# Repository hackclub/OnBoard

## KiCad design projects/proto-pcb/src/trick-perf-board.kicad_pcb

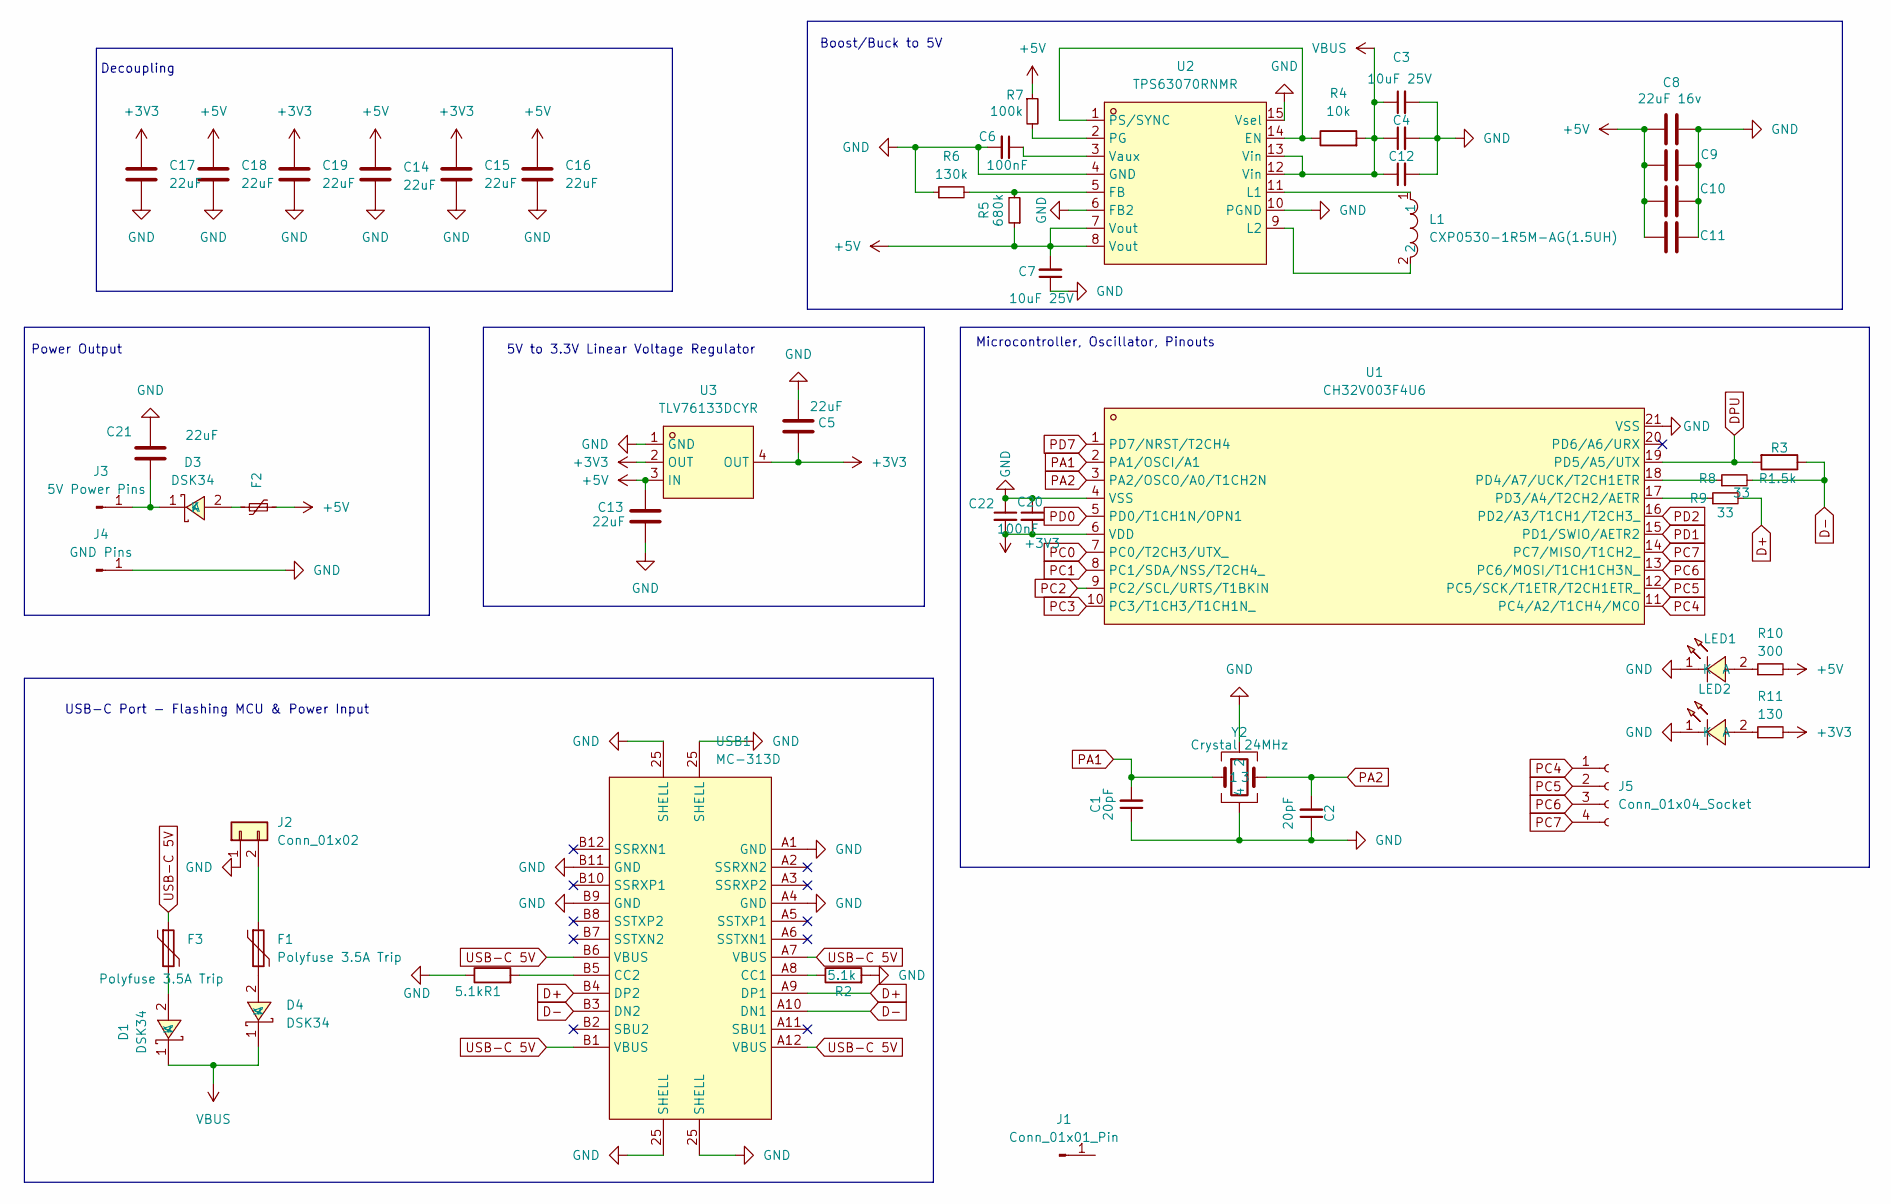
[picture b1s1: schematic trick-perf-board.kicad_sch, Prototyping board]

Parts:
C1, C2: 20pF; C_0402_1005Metric; LCSC C880615
C3, C4, C7, C12: 10uF 25V; C_0603_1608Metric; LCSC Part C7393892
C5, C13, C21: 22uF; C_0603_1608Metric; LCSC Part C6119880
C6, C20, C22: 100nF; C_0402_1005Metric; LCSC Part C392963
C8, C9, C10, C11: 22uF 16v; C_0603_1608Metric; LCSC Part C6119868
C14, C15, C16, C17, C18, C19: 22uF; C_0805_2012Metric; LCSC Part C6119899
D1, D3, D4: DSK34; SOD-123_L2.8-W1.8-LS3.7-RD; LCSC Part C41029
F1, F3: Polyfuse 3.5A Trip; Fuse_1206_3216Metric; LCSC Part C2982271
F2: Polyfuse_Small; Fuse_0603_1608Metric; LCSC Part C2830225
J1: Conn_01x01_Pin; LargePerfBoard
J2: Conn_01x02; PinSocket_1x02_P2.54mm_Horizontal
J3: 5V Power Pins; customPerfBoardpins
J4: GND Pins; customPerfBoardpins
J5: Conn_01x04_Socket; PinHeader_1x04_P2.54mm_Vertical
L1: CXP0530-1R5M-AG(1.5UH); L_0603_1608Metric; LCSC Part C7461358
LED1, LED2: TZ-P2-0402RTIA1-0.45T; LED0402-RD_RED; LCSC Part C779449
R1, R2: 5.1k; R_0402_1005Metric; LCSC Part C103086
R3: R1.5k; R_0402_1005Metric; LCSC Part C2929900
R4: 10k; R_0402_1005Metric; LCSC Part C2906885
R5: 680k; R_0402_1005Metric; LCSC Part C3017522
R6: 130k; R_0402_1005Metric; LCSC Part C2909318
R7: 100k; R_0402_1005Metric; LCSC Part C2759534
R8, R9: 33; R_0402_1005Metric; LCSC Part C2906931
R10: 300; R_0402_1005Metric; LCSC Part C352438
R11: 130; R_0402_1005Metric; LCSC Part C352478
U1: CH32V003F4U6; QFN-20-1EP_3x3mm_P0.4mm_EP1.65x1.65mm; LCSC Part C5299908
U2: TPS63070RNMR; VQFN-HR-15_L3.0-W2.5-P0.50-BL_TPS63070RNMR; LCSC Part C109322
U3: TLV76133DCYR; SOT-223-4_L6.5-W3.5-P2.30-LS7.0-TR; LCSC Part C7527500
USB1: MC-313D; TYPE-C-TH_MC-313D; LCSC Part C428461
Y2: Crystal 24MHz; Crystal_SMD_2016-4Pin_2.0x1.6mm; LCSC Part C2875241

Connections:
+3V3: C5.1, C15.1, C17.1, C19.1, C20.2, C22.2, R11.2, U1.6 (VDD), U3.2 (OUT), U3.4 (OUT)
+5V: C7.2, C8.1, C9.1, C10.1, C11.1, C13.1, C14.1, C16.1, C18.1, F2.2, R5.1, R7.1, R10.2, U2.7 (Vout), U2.8 (Vout), U3.3 (IN)
D+: R9.2, USB1.A9 (DP1), USB1.B4 (DP2)
D-: R3.1, R8.2, USB1.A10 (DN1), USB1.B3 (DN2)
DPU: R3.2, U1.19 (PD5/A5/UTX)
GND: C1.1, C2.1, C3.2, C4.2, C5.2, C6.2, C7.1, C8.2, C9.2, C10.2, C11.2, C12.2, C13.2, C14.2, C15.2, C16.2, C17.2, C18.2, C19.2, C20.1, C21.1, C22.1, J2.1, J4.1, LED1.1 (K), LED2.1 (K), R1.1, R2.2, R6.1, U1.4 (VSS), U1.21 (VSS), U2.4 (GND), U2.6 (FB2), U2.10 (PGND), U2.15 (Vsel), U3.1 (GND), USB1.25 (SHELL), USB1.A1 (GND), USB1.A4 (GND), USB1.B9 (GND), USB1.B11 (GND), Y2.2, Y2.4
unnamed: D1.2 (A), F3.2
unnamed: D3.2 (A), F2.1
unnamed: C21.2, D3.1 (K), J3.1
unnamed: D4.2 (A), F1.2
unnamed: F1.1, J2.2
unnamed: LED1.2 (A), R10.1
unnamed: LED2.2 (A), R11.1
unnamed: R9.1, U1.17 (PD3/A4/T2CH2/AETR)
unnamed: R8.1, U1.18 (PD4/A7/UCK/T2CH1ETR)
unnamed: R4.1, U2.1 (PS/SYNC), U2.14 (EN)
unnamed: R5.2, R6.2, U2.5 (FB)
unnamed: L1.1, U2.11 (L1)
unnamed: L1.2, U2.9 (L2)
unnamed: R7.2, U2.2 (PG)
unnamed: C6.1, U2.3 (Vaux)
unnamed: R2.1, USB1.A8 (CC1)
unnamed: R1.2, USB1.B5 (CC2)
PA1: C1.2, U1.2 (PA1/OSCI/A1), Y2.1
PA2: C2.2, U1.3 (PA2/OSCO/A0/T1CH2N), Y2.3
PC0: U1.7 (PC0/T2CH3/UTX_)
PC1: U1.8 (PC1/SDA/NSS/T2CH4_)
PC2: U1.9 (PC2/SCL/URTS/T1BKIN)
PC3: U1.10 (PC3/T1CH3/T1CH1N_)
PC4: J5.1, U1.11 (PC4/A2/T1CH4/MCO)
PC5: J5.2, U1.12 (PC5/SCK/T1ETR/T2CH1ETR_)
PC6: J5.3, U1.13 (PC6/MOSI/T1CH1CH3N_)
PC7: J5.4, U1.14 (PC7/MISO/T1CH2_)
PD0: U1.5 (PD0/T1CH1N/OPN1)
PD1: U1.15 (PD1/SWIO/AETR2)
PD2: U1.16 (PD2/A3/T1CH1/T2CH3_)
PD7: U1.1 (PD7/NRST/T2CH4)
USB-C 5V: F3.1, USB1.A7 (VBUS), USB1.A12 (VBUS), USB1.B1 (VBUS), USB1.B6 (VBUS)
VBUS: C3.1, C4.1, C12.1, D1.1 (K), D4.1 (K), R4.2, U2.12 (Vin), U2.13 (Vin)

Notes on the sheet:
Microcontroller, Oscillator, Pinouts
5V to 3.3V Linear Voltage Regulator
Decoupling
USB-C Port - Flashing MCU & Power Input
Boost/Buck to 5V
Power Output

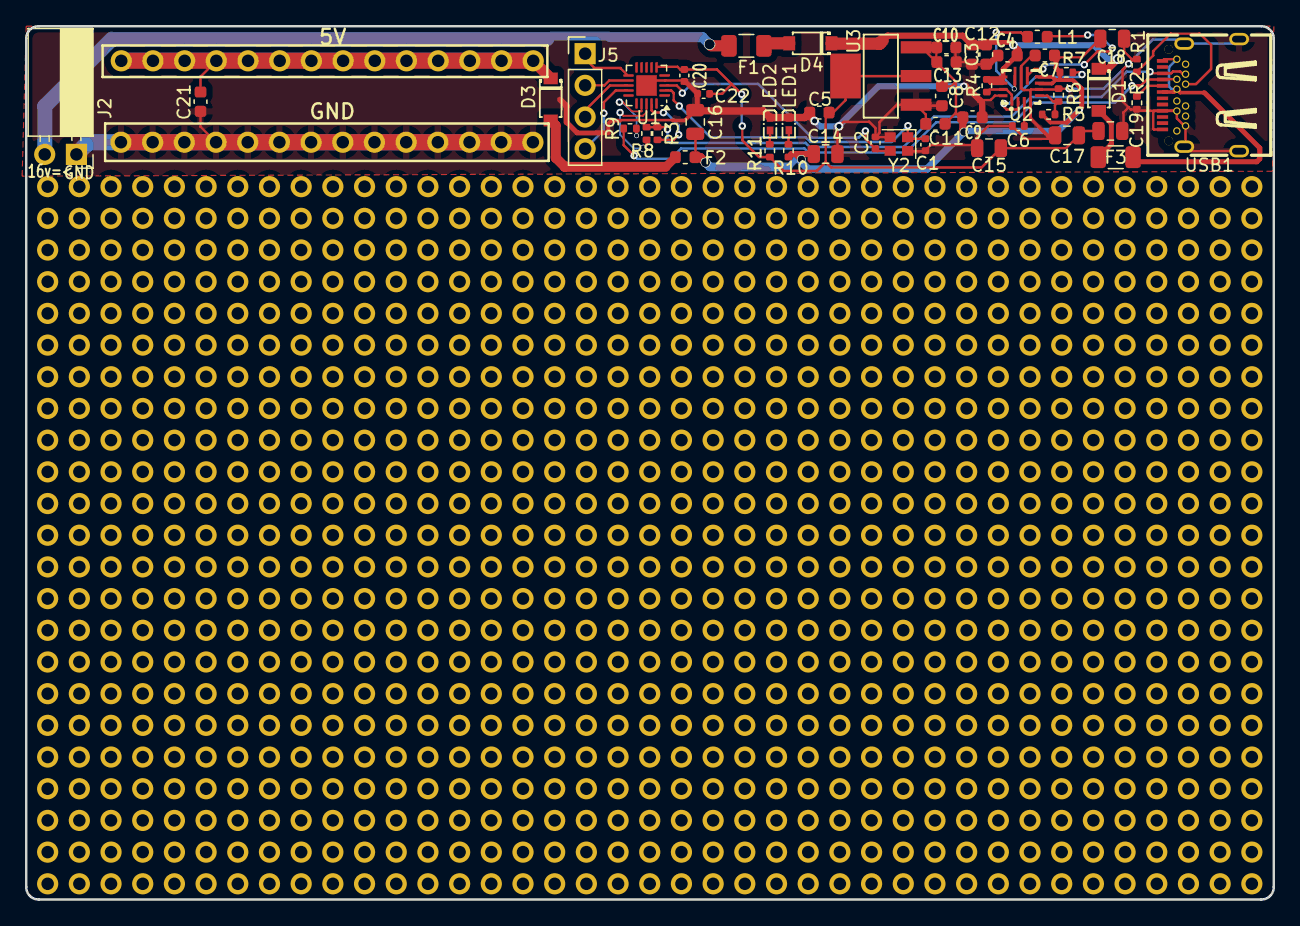
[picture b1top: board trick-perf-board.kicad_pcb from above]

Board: 2 copper layers, 100.0 x 70.0 mm, 52 parts (0 on the bottom side), 31 nets.

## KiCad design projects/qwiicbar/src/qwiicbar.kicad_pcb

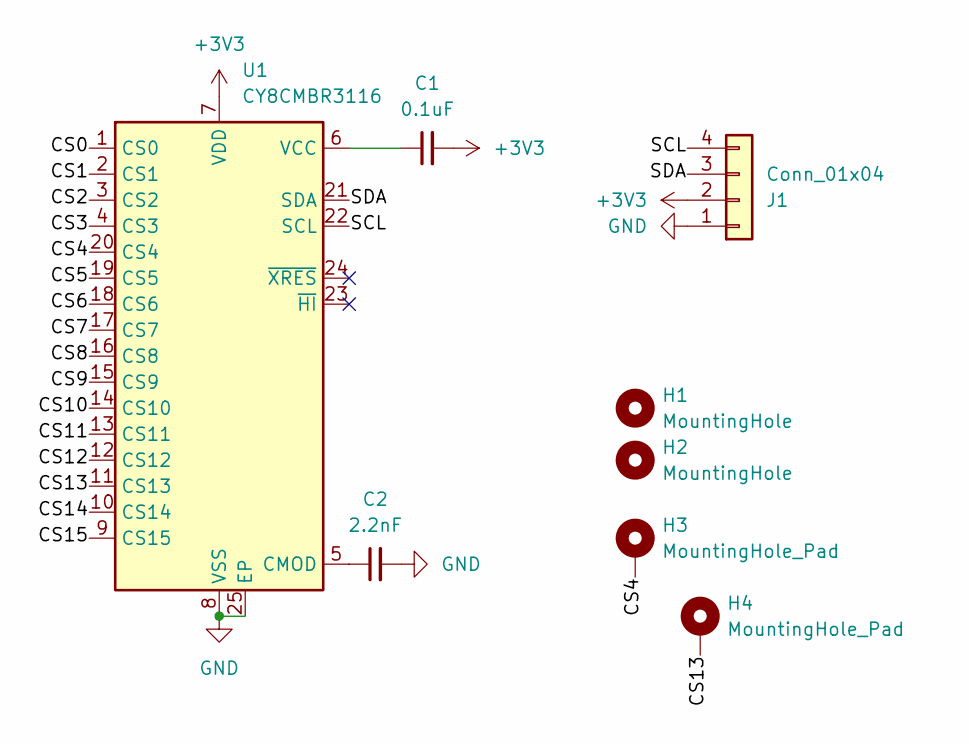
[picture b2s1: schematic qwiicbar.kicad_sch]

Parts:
C1: 0.1uF; C_0603_1608Metric
C2: 2.2nF; C_0805_2012Metric
H1, H2: MountingHole; JLCPCB_PCBA_ToolingHole
H3, H4: MountingHole_Pad; MountingHole_2.2mm_M2_ISO7380_Pad
J1: Conn_01x04; JST_SH_SM04B-SRSS-TB_1x04-1MP_P1.00mm_Horizontal
U1: CY8CMBR3116; QFN-24-1EP_4x4mm_P0.5mm_EP2.6x2.6mm

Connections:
+3V3: C1.2, J1.2, U1.7 (VDD)
/CS0: U1.1 (CS0)
/CS1: U1.2 (CS1)
/CS2: U1.3 (CS2)
/CS3: U1.4 (CS3)
/CS4: H3.1, U1.20 (CS4)
/CS5: U1.19 (CS5)
/CS6: U1.18 (CS6)
/CS7: U1.17 (CS7)
/CS8: U1.16 (CS8)
/CS9: U1.15 (CS9)
/CS10: U1.14 (CS10)
/CS11: U1.13 (CS11)
/CS12: U1.12 (CS12)
/CS13: H4.1, U1.11 (CS13)
/CS14: U1.10 (CS14)
/CS15: U1.9 (CS15)
/SCL: J1.4, U1.22 (SCL)
/SDA: J1.3, U1.21 (SDA)
GND: C2.2, J1.1, U1.8 (VSS), U1.25 (EP)
unnamed: C2.1, U1.5 (CMOD)
unnamed: C1.1, U1.6 (VCC)

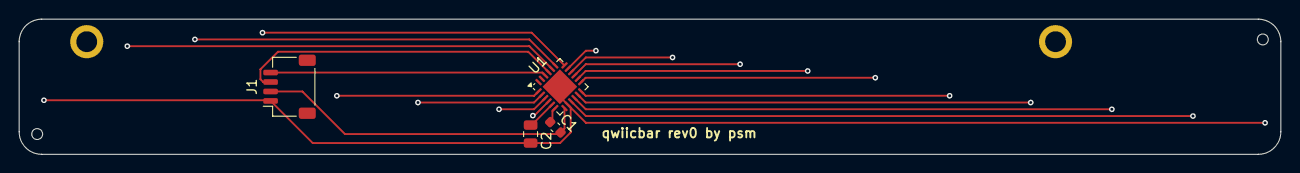
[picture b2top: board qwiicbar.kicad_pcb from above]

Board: 2 copper layers, 133.3 x 14.3 mm, 8 parts (0 on the bottom side), 8 nets.

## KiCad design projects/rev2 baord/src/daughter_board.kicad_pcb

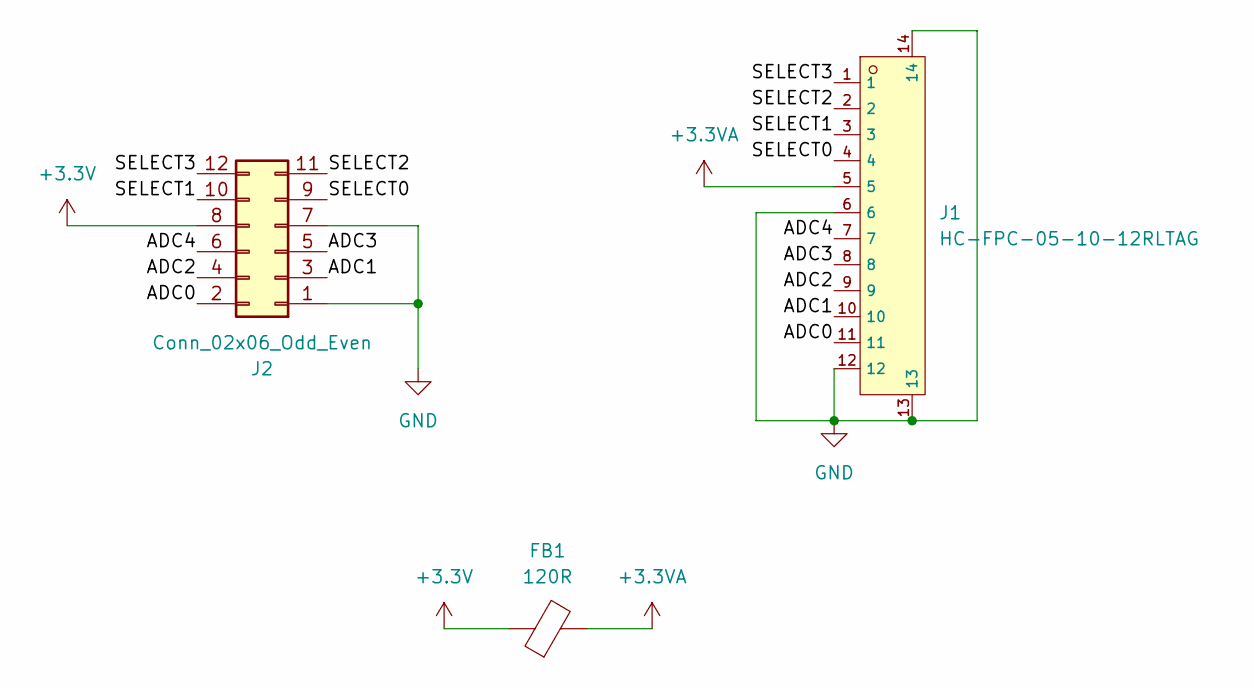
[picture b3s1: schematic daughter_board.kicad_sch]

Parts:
FB1: 120R; L_0603_1608Metric_Pad1.05x0.95mm_HandSolder; LCSC C76892
J1: HC-FPC-05-10-12RLTAG; FPC-SMD_12P-P0.50_HCTL_HC-FPC-05-10-12RLTAG; LCSC C5213732
J2: Conn_02x06_Odd_Even; PinHeader_2x06_P2.54mm_Horizontal

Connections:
+3.3V: FB1.1, J2.8
+3.3VA: FB1.2, J1.5
/ADC0: J1.11, J2.2
/ADC1: J1.10, J2.3
/ADC2: J1.9, J2.4
/ADC3: J1.8, J2.5
/ADC4: J1.7, J2.6
/SELECT0: J1.4, J2.9
/SELECT1: J1.3, J2.10
/SELECT2: J1.2, J2.11
/SELECT3: J1.1, J2.12
GND: J1.6, J1.12, J1.13, J1.14, J2.1, J2.7

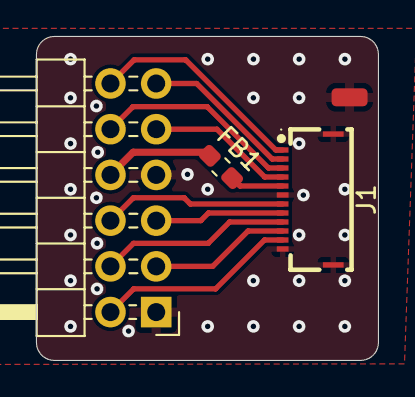
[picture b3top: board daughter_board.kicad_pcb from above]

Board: 2 copper layers, 19.0 x 18.0 mm, 3 parts (0 on the bottom side), 12 nets.

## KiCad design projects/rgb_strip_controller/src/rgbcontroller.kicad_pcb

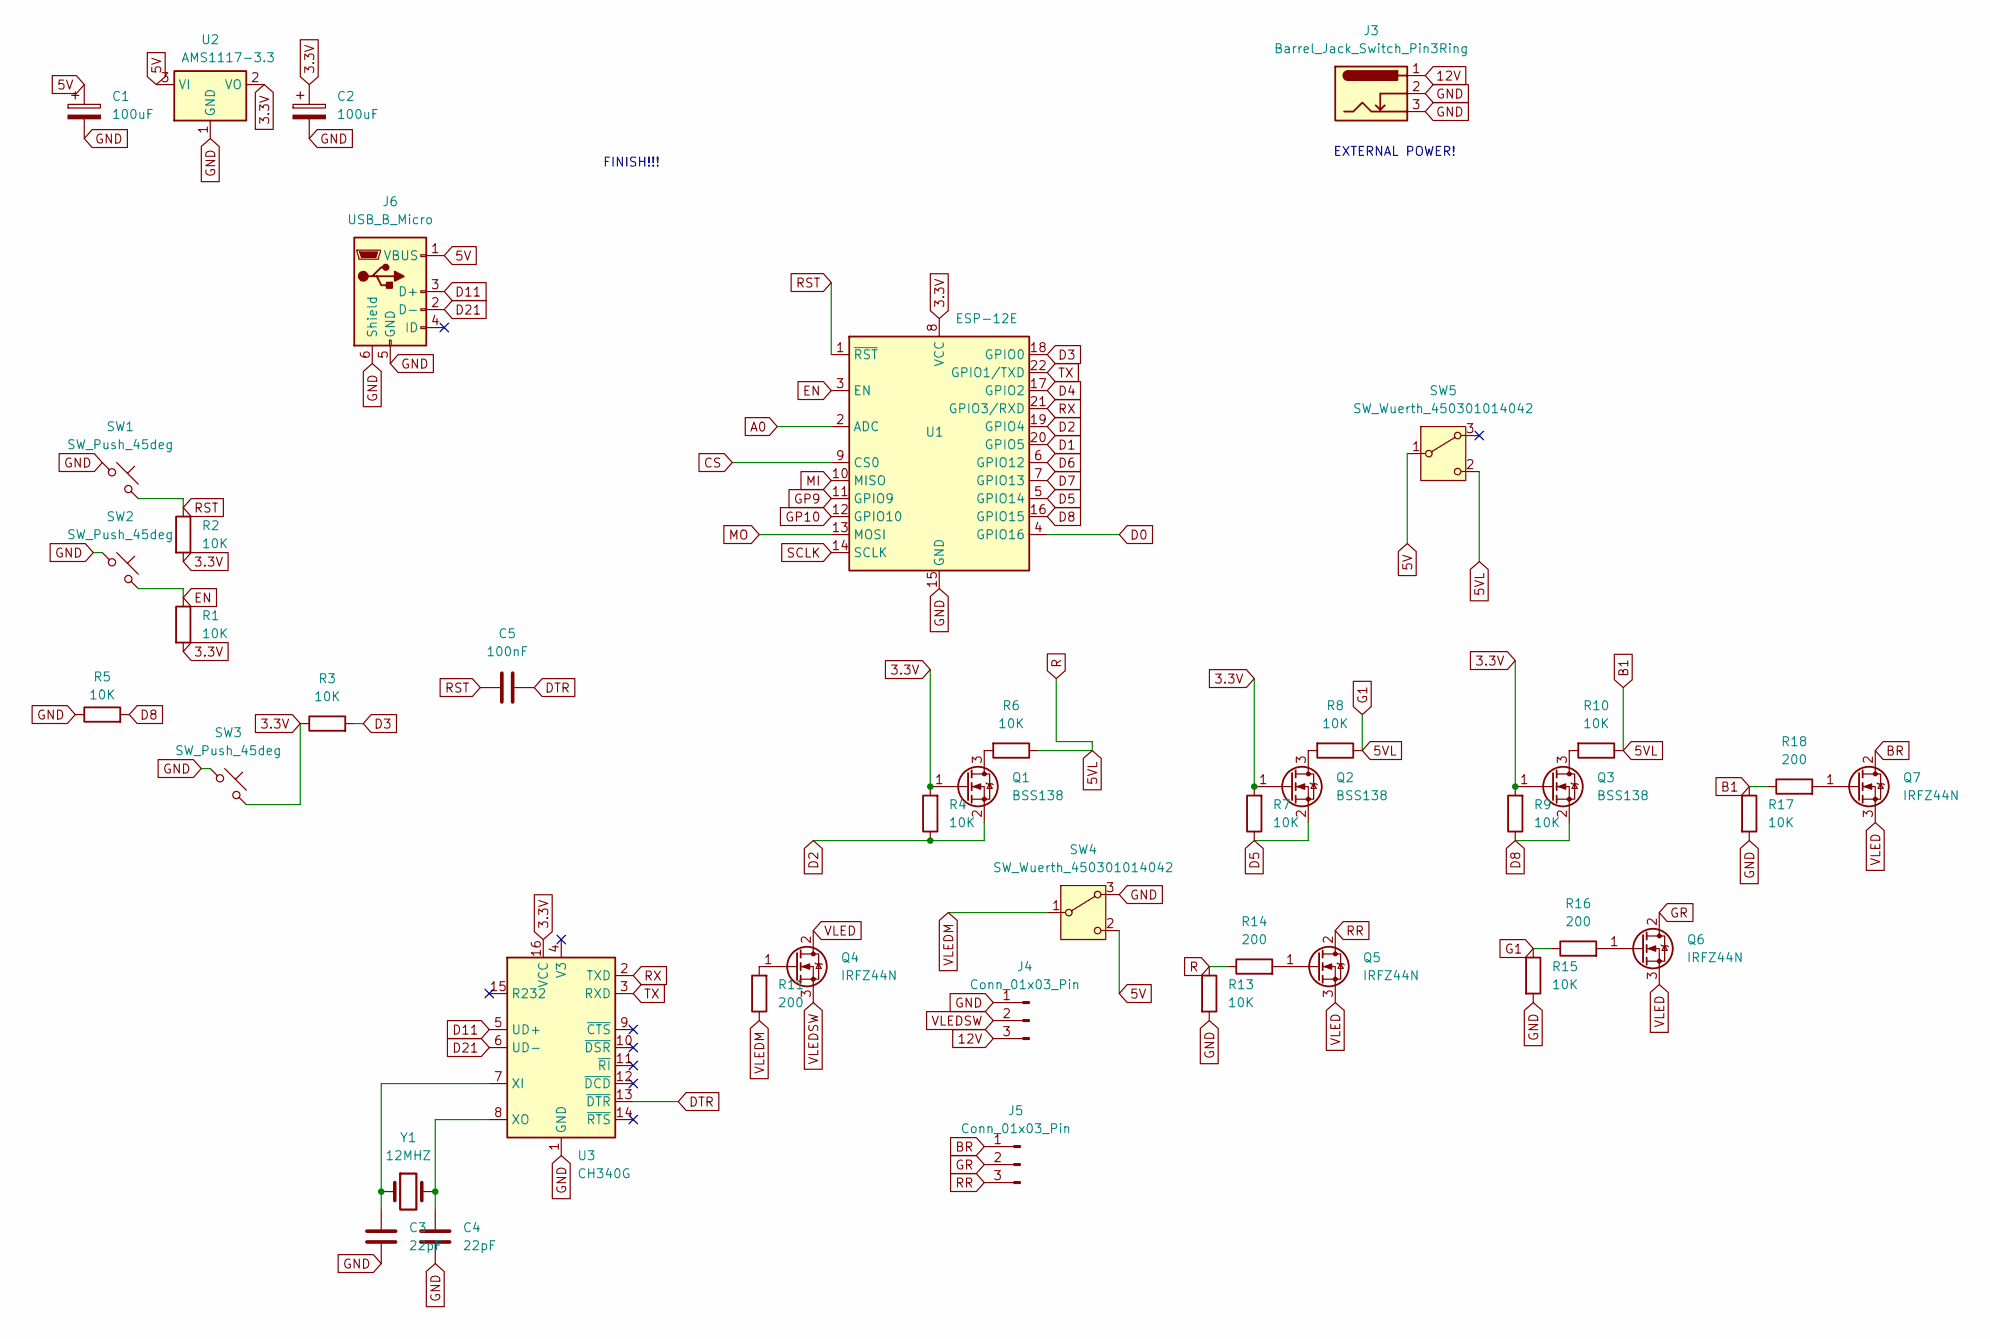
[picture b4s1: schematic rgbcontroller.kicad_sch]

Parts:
C1, C2: 100uF; CP_Radial_D4.0mm_P1.50mm
C3, C4: 22pF; C_0805_2012Metric_Pad1.18x1.45mm_HandSolder
C5: 100nF; C_0805_2012Metric_Pad1.18x1.45mm_HandSolder
J3: Barrel_Jack_Switch_Pin3Ring; BarrelJack_GCT_DCJ200-10-A_Horizontal
J4, J5: Conn_01x03_Pin; PinHeader_1x03_P2.54mm_Vertical
J6: USB_B_Micro; USB_Micro-B_Amphenol_10118193-0001LF_Horizontal
Q1, Q2, Q3: BSS138; SOT-23
Q4, Q5, Q6, Q7: IRFZ44N; TO-220-3_Vertical
R1, R2, R3, R4, R5, R6, R7, R8, R9, R10, R13, R15, R17: 10K; R_0805_2012Metric_Pad1.20x1.40mm_HandSolder
R11, R14, R16, R18: 200; R_0805_2012Metric_Pad1.20x1.40mm_HandSolder
SW1, SW2, SW3: SW_Push_45deg; SW_PUSH_6mm
SW4, SW5: SW_Wuerth_450301014042; SW_Slide-03_Wuerth-WS-SLTV_10x2.5x6.4_P2.54mm
U1: ESP-12E
U2: AMS1117-3.3; SOT-223-3_TabPin2
U3: CH340G; SOIC-16_3.9x9.9mm_P1.27mm
Y1: 12MHZ; Crystal_HC49-4H_Vertical

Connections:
3.3V: C2.1, Q1.1 (G), Q2.1 (G), Q3.1 (G), R1.2, R2.2, R3.1, R4.2, R7.2, R9.2, SW3.2, U1.8 (VCC), U2.2 (VO), U3.16 (VCC)
5V: C1.1, J6.1 (VBUS), SW4.2 (C), SW5.1 (B), U2.3 (VI)
5VL: R6.1, R8.1, R10.1, R13.1, R14.1, R15.1, R16.1, R17.1, R18.1, SW5.2 (C)
12V: J3.1, J4.3
A0: U1.2 (ADC)
BR: J5.1, Q7.2 (D)
CS: U1.9 (CS0)
D0: U1.4 (GPIO16)
D1: U1.20 (GPIO5)
D2: Q1.2 (S), R4.1, U1.19 (GPIO4)
D3: R3.2, U1.18 (GPIO0)
D4: U1.17 (GPIO2)
D5: Q2.2 (S), R7.1, U1.5 (GPIO14)
D6: U1.6 (GPIO12)
D7: U1.7 (GPIO13)
D8: Q3.2 (S), R5.2, R9.1, U1.16 (GPIO15)
D11: J6.3 (D+), U3.5 (UD+)
D21: J6.2 (D-), U3.6 (UD-)
DTR: C5.1, U3.13 (~DTR)
EN: R1.1, SW2.2, U1.3 (EN)
GND: C1.2, C2.2, C3.2, C4.2, J3.2, J3.3, J4.1, J6.5 (GND), J6.6 (Shield), R5.1, R13.2, R15.2, R17.2, SW1.1, SW2.1, SW3.1, SW4.3 (A), U1.15 (GND), U2.1 (GND), U3.1 (GND)
GP9: U1.11 (GPIO9)
GP10: U1.12 (GPIO10)
GR: J5.2, Q6.2 (D)
MI: U1.10 (MISO)
MO: U1.13 (MOSI)
unnamed: Q1.3 (D), R6.2
unnamed: Q2.3 (D), R8.2
unnamed: Q3.3 (D), R10.2
unnamed: Q4.1 (G), R11.2
unnamed: Q5.1 (G), R14.2
unnamed: Q6.1 (G), R16.2
unnamed: Q7.1 (G), R18.2
unnamed: C3.1, U3.7 (XI), Y1.1
unnamed: C4.1, U3.8 (XO), Y1.2
RR: J5.3, Q5.2 (D)
RST: C5.2, R2.1, SW1.2, U1.1 (~RST)
RX: U1.21 (GPIO3/RXD), U3.2 (TXD)
SCLK: U1.14 (SCLK)
TX: U1.22 (GPIO1/TXD), U3.3 (RXD)
VLED: Q4.2 (D), Q5.3 (S), Q6.3 (S), Q7.3 (S)
VLEDM: R11.1, SW4.1 (B)
VLEDSW: J4.2, Q4.3 (S)

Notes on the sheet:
FINISH!!!
EXTERNAL POWER!

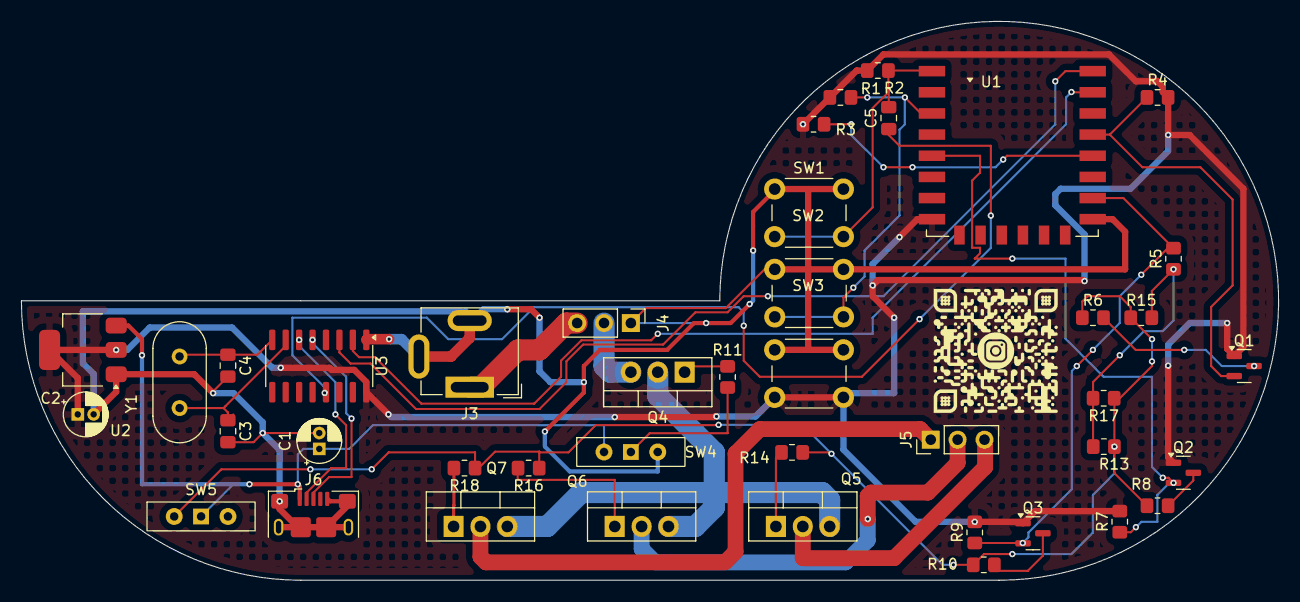
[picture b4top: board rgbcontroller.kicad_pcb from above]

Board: 2 copper layers, 118.9 x 52.8 mm, 42 parts (0 on the bottom side), 31 nets.

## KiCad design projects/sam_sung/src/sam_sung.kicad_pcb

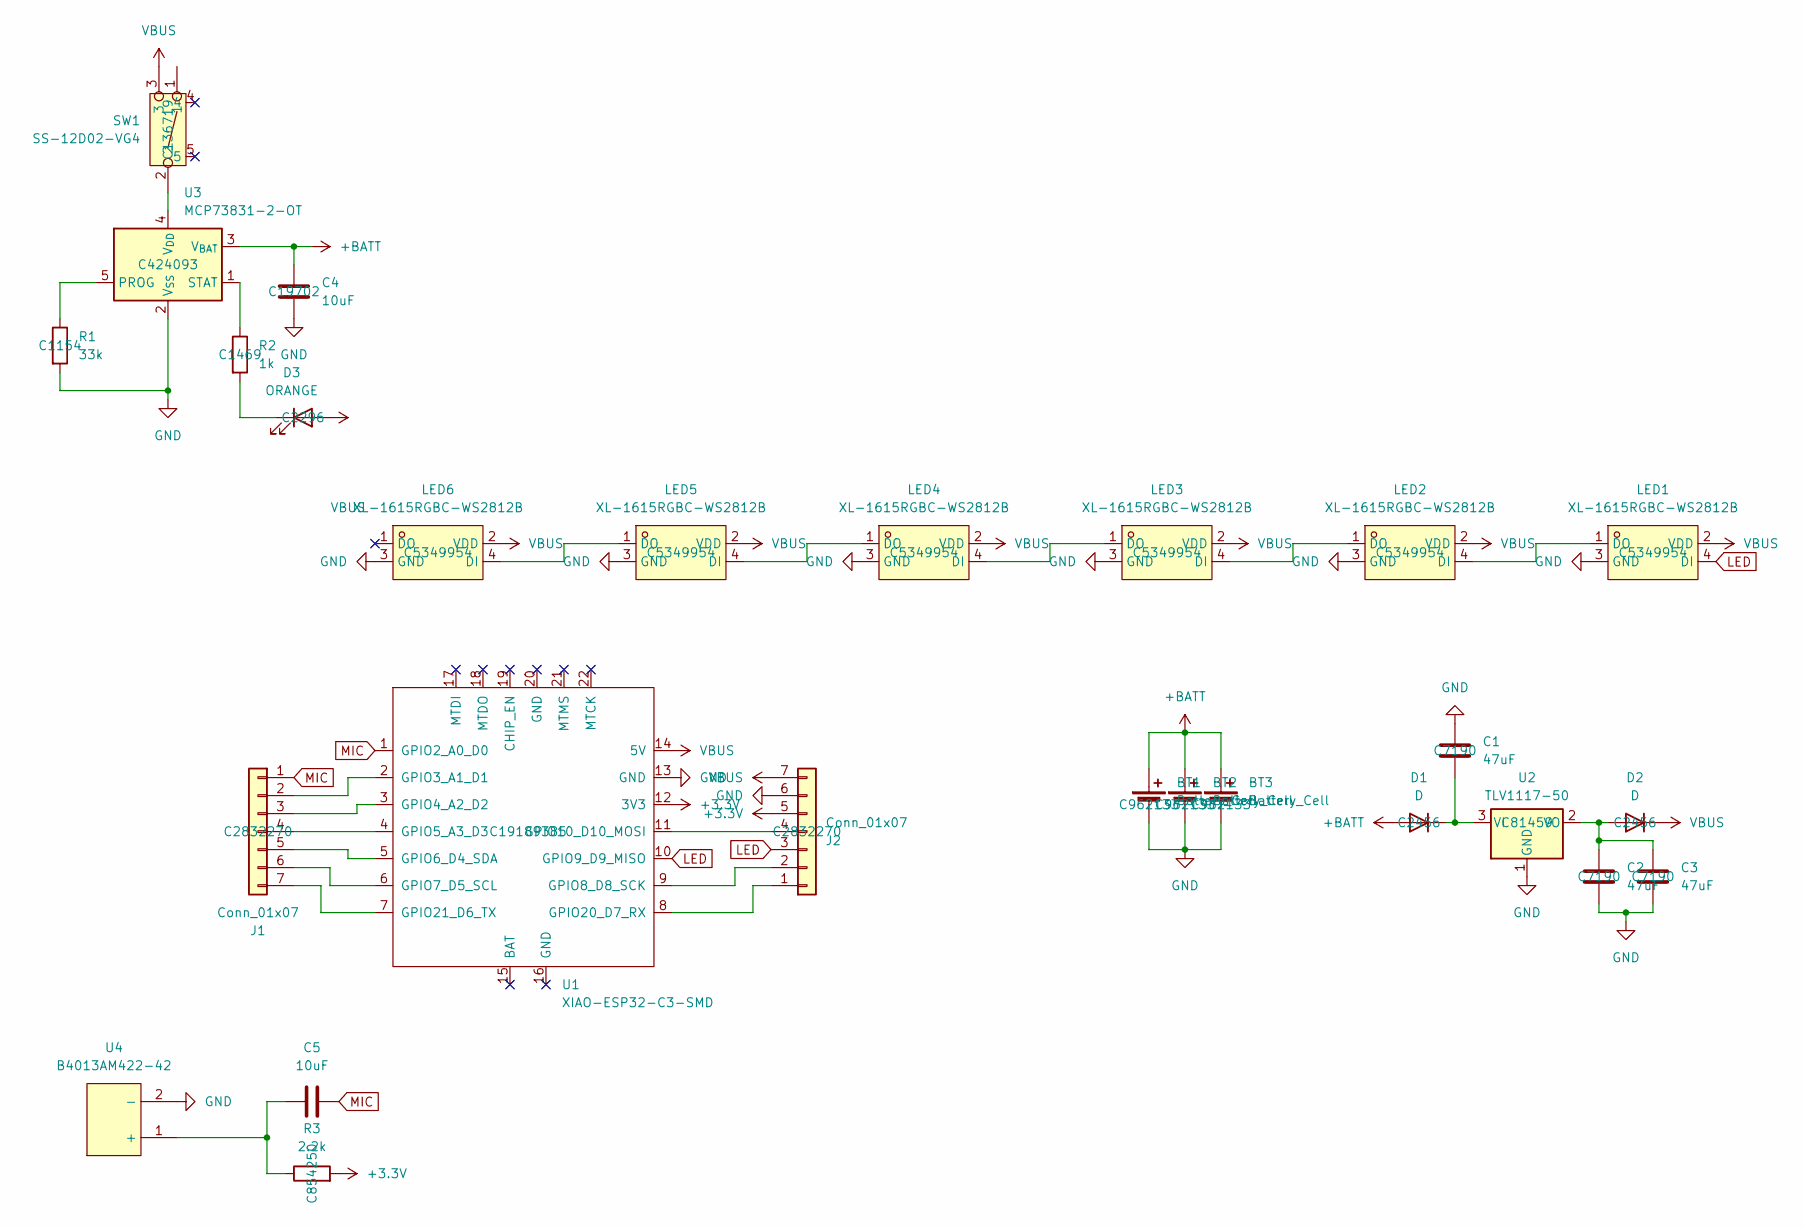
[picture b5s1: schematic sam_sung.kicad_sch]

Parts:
BT1, BT2, BT3: Battery_Cell; BAT-TH_AAA-BAT-029-K01; LCSC C962133
C1, C2, C3: 47uF; CASE-A_3216; LCSC C7190
C4: 10uF; C0603; LCSC C19702
C5: 10uF; C0603
D1, D2: D; DO-41_BD2.4-L4.7-P8.70-D0.9-RD; LCSC C2456
D3: ORANGE; LED0805-R-RD; LCSC C2296
J1, J2: Conn_01x07; HDR-TH_7P-P2.54-V-F; LCSC C2832270
LED1, LED2, LED3, LED4, LED5, LED6: XL-1615RGBC-WS2812B; LED-SMD_4P-L1.6-W1.5_XL-1615RGBC-WS2812B; LCSC Part C5349954
R1: 33k; R0402; LCSC C1154
R2: 1k; R1206; LCSC C1469
R3: 2.2k; R0402; LCSC C854250
SW1: SS-12D02-VG4; SW-TH_SS-12D02-VG4; LCSC C136719
U1: XIAO-ESP32-C3-SMD; XIAO-ESP32S3-SMD; LCSC C19189385
U2: TLV1117-50; SOT-223_L6.5-W3.5-P2.30-LS7.0-BR; LCSC C81459
U3: MCP73831-2-OT; SOT-23-5; LCSC C424093
U4: B4013AM422-42; CUI_CMC-4013-SMT; LCSC Part C233793

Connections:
+3.3V: J2.5, R3.2, U1.12 (3V3)
+BATT: BT1.1 (+), BT2.1 (+), BT3.1 (+), C4.1, D1.2 (A), U3.3 (V_{BAT})
GND: BT1.2 (-), BT2.2 (-), BT3.2 (-), C1.1, C2.2, C3.2, C4.2, J2.6, LED1.3 (GND), LED2.3 (GND), LED3.3 (GND), LED4.3 (GND), LED5.3 (GND), LED6.3 (GND), R1.2, U1.13 (GND), U2.1 (GND), U3.2 (V_{SS}), U4.2 (-)
LED: J2.3, LED1.4 (DI), U1.10 (GPIO9_D9_MISO)
MIC: C5.2, J1.1, U1.1 (GPIO2_A0_D0)
unnamed: C1.2, D1.1 (K), U2.3 (VI)
unnamed: C2.1, C3.1, D2.2 (A), U2.2 (VO)
unnamed: D3.1 (K), R2.2
unnamed: J1.2, U1.2 (GPIO3_A1_D1)
unnamed: J1.3, U1.3 (GPIO4_A2_D2)
unnamed: J1.4, U1.4 (GPIO5_A3_D3)
unnamed: J1.5, U1.5 (GPIO6_D4_SDA)
unnamed: J1.6, U1.6 (GPIO7_D5_SCL)
unnamed: J1.7, U1.7 (GPIO21_D6_TX)
unnamed: J2.1, U1.8 (GPIO20_D7_RX)
unnamed: J2.2, U1.9 (GPIO8_D8_SCK)
unnamed: J2.4, U1.11 (GPIO10_D10_MOSI)
unnamed: LED1.1 (DO), LED2.4 (DI)
unnamed: LED2.1 (DO), LED3.4 (DI)
unnamed: LED3.1 (DO), LED4.4 (DI)
unnamed: LED4.1 (DO), LED5.4 (DI)
unnamed: LED5.1 (DO), LED6.4 (DI)
unnamed: R1.1, U3.5 (PROG)
unnamed: R2.1, U3.1 (STAT)
unnamed: SW1.2, U3.4 (V_{DD})
unnamed: C5.1, R3.1, U4.1 (+)
VBUS: D2.1 (K), D3.2 (A), J2.7, LED1.2 (VDD), LED2.2 (VDD), LED3.2 (VDD), LED4.2 (VDD), LED5.2 (VDD), LED6.2 (VDD), SW1.3, U1.14 (5V)

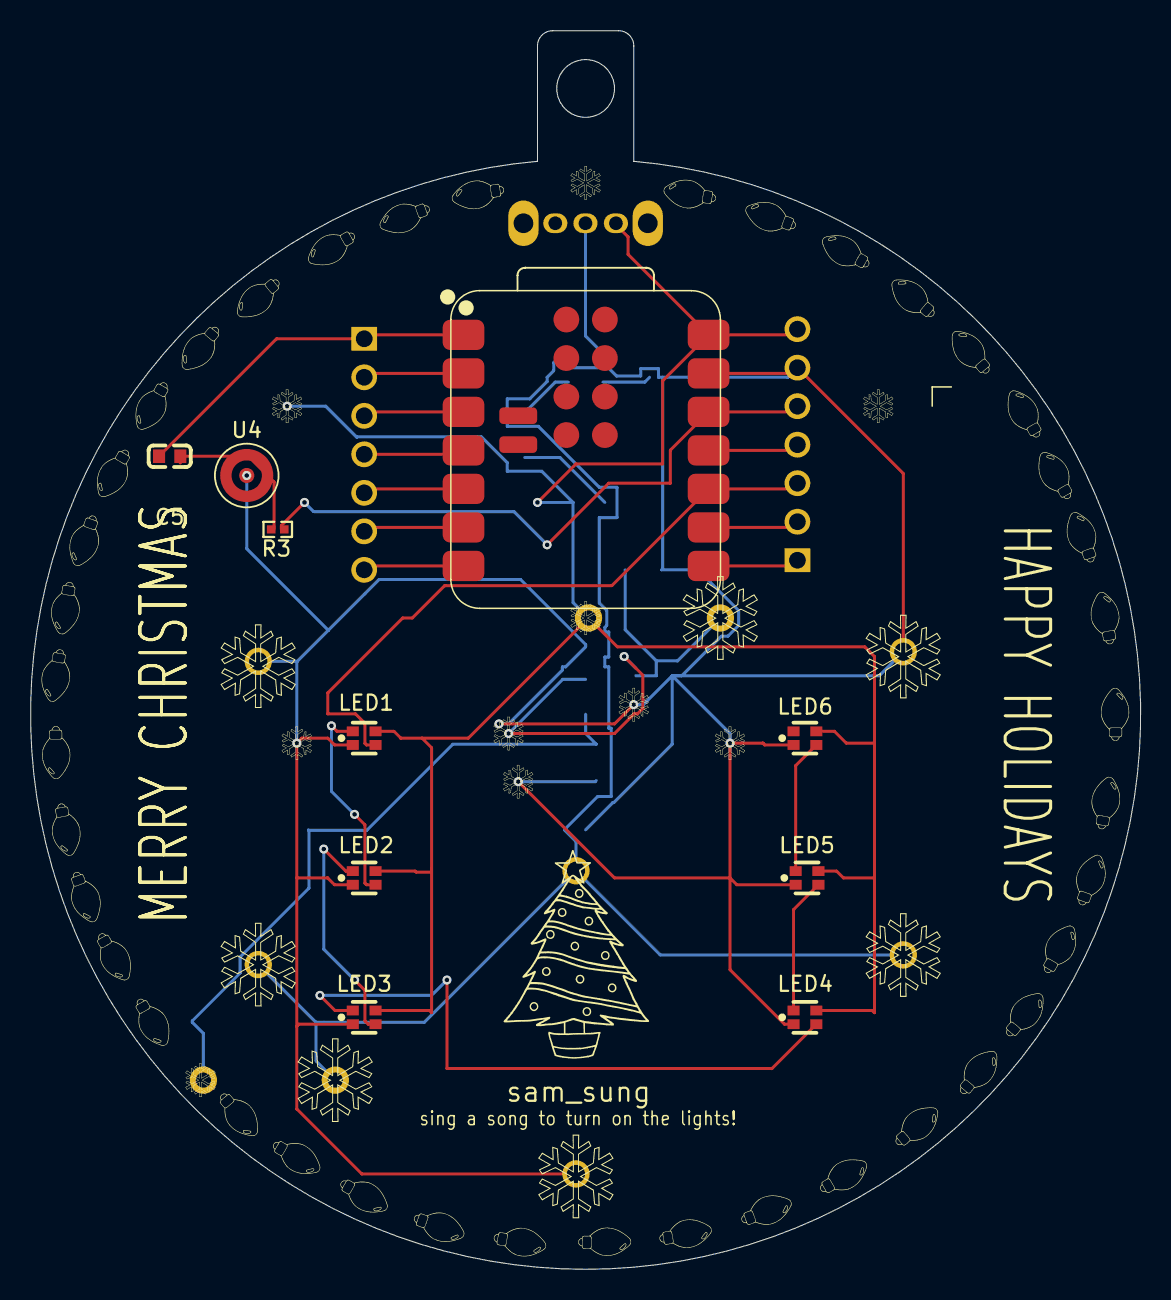
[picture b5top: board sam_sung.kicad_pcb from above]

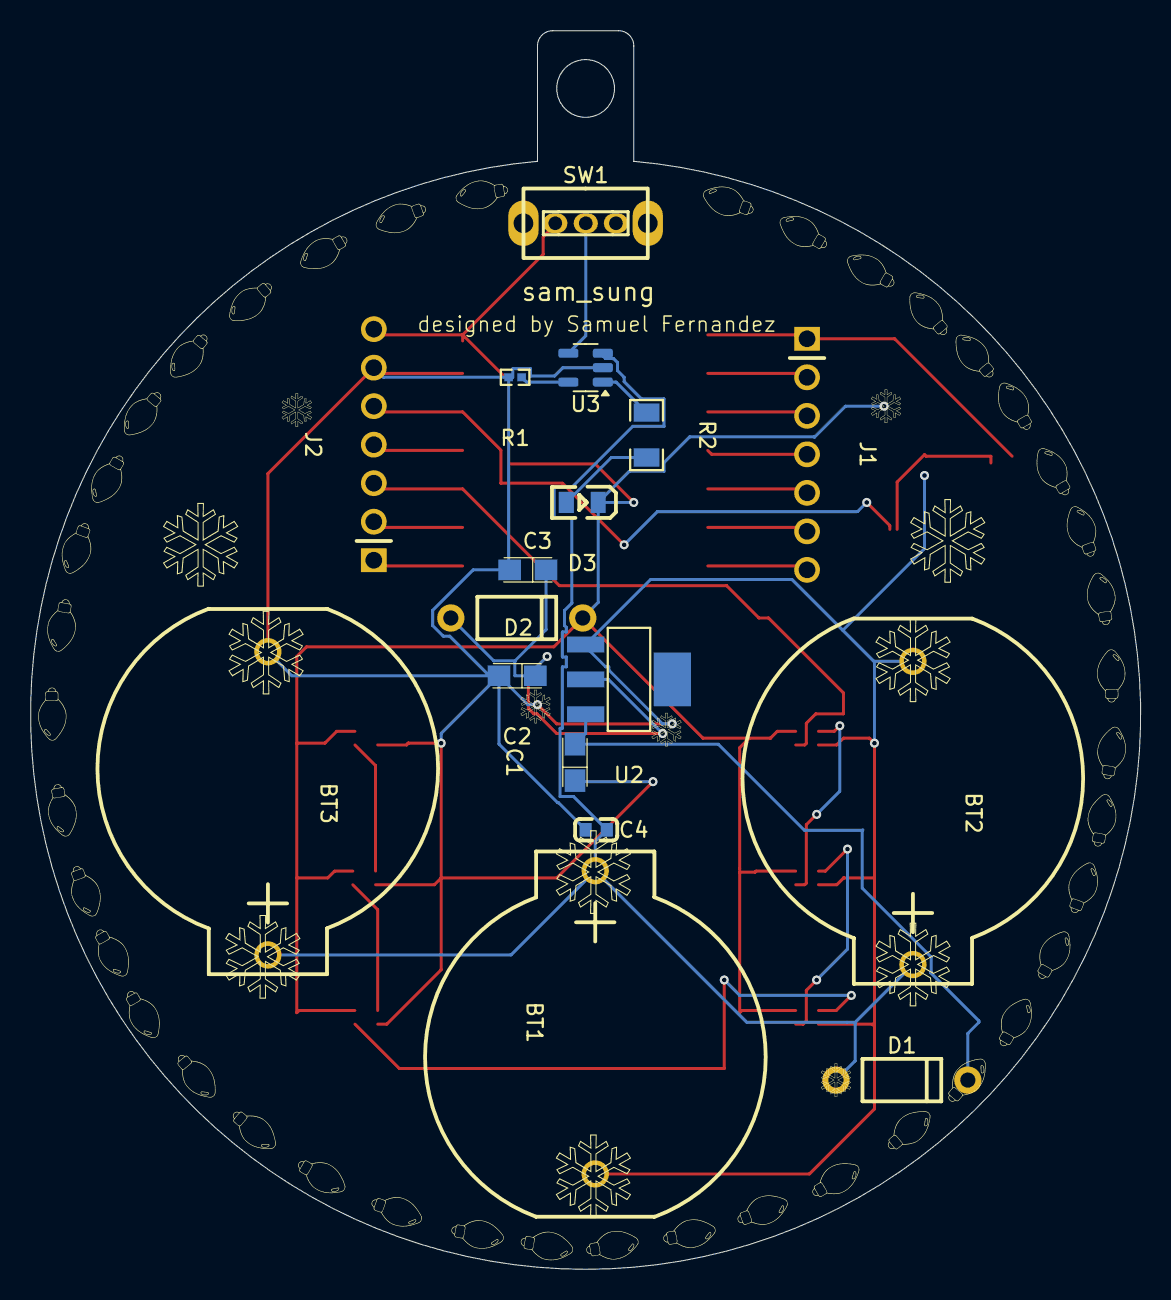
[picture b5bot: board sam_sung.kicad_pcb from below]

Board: 2 copper layers, 73.2 x 81.7 mm, 27 parts (17 on the bottom side), 27 nets.

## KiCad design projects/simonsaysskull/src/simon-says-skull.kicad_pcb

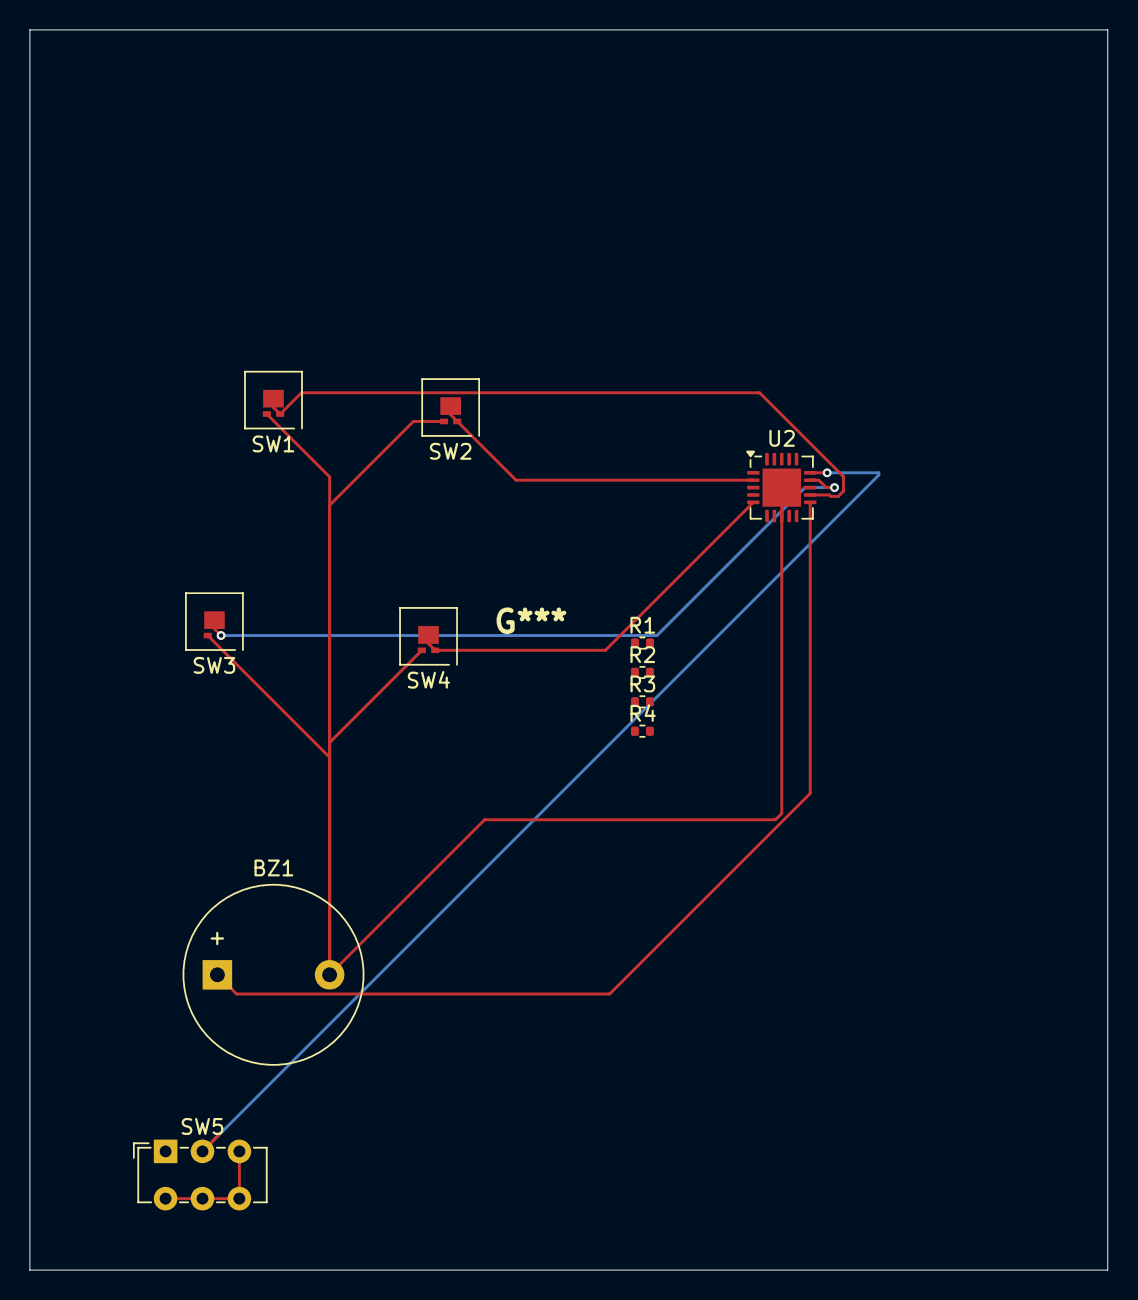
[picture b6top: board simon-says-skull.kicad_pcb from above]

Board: 2 copper layers, 73.0 x 84.0 mm, 11 parts (0 on the bottom side), 8 nets.

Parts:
BZ1: Buzzer; Buzzer_12x9.5RM7.6
R1, R2, R3, R4: 330; R_0402_1005Metric
SW1, SW2, SW3, SW4: SW_Push_LED; LED-L1T2_LUMILEDS
SW5: SW_DPST_x2; SW_E-Switch_EG1271_SPDT
U2: ATtiny85-20M; QFN-20-1EP_4x4mm_P0.5mm_EP2.6x2.6mm

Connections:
GND: BZ1.2 (-), SW1.2, SW2.2, SW3.2, SW4.2, U2.8 (GND), U2.21 (GND)
unnamed: BZ1.1 (+), U2.11 (AREF/PB0)
unnamed: R1.1, R2.1, R3.1, R4.1
unnamed: SW1.1, SW1.3 (K), U2.12 (PB1)
unnamed: SW2.1, SW2.3 (K), U2.2 (XTAL1/PB3)
unnamed: SW3.1, SW3.3 (K), U2.14 (PB2)
unnamed: SW4.1, SW4.3 (K), U2.5 (XTAL2/PB4)
unnamed: SW5.2 (B), U2.15 (VCC)
